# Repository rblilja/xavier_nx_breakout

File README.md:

# xavier_nx_breakout
Header breakout for NVIDIA Jetson Xavier NX Development Kit.

This breakout board overcomes the limitation of the 2uA maximum output current (per pin) of the TXB0108 8-Bit Bidirectional Voltage-Level Translators used for the GPIOs of the J12 header.

The breakout provides the following:

* UART1_TX and UART1_RTS buffered with non-inverting Schmitt triggers.
* PWM capable GPIO07, GPIO12 and GPIO13 buffered with non-inverting Schmitt triggers.
* Pixhawk compatible interface (JST-GH 6-pin 1.25 mm pitch) provided for UART1.
* Stemma QT / Qwiic (JST-SH 4-pin 1.0 mm pitch) compatible interface provided for I2C0.
* Pixhawk compatible interface (JST-GH 4-pin 1.25 mm pitch) provided for I2C1.

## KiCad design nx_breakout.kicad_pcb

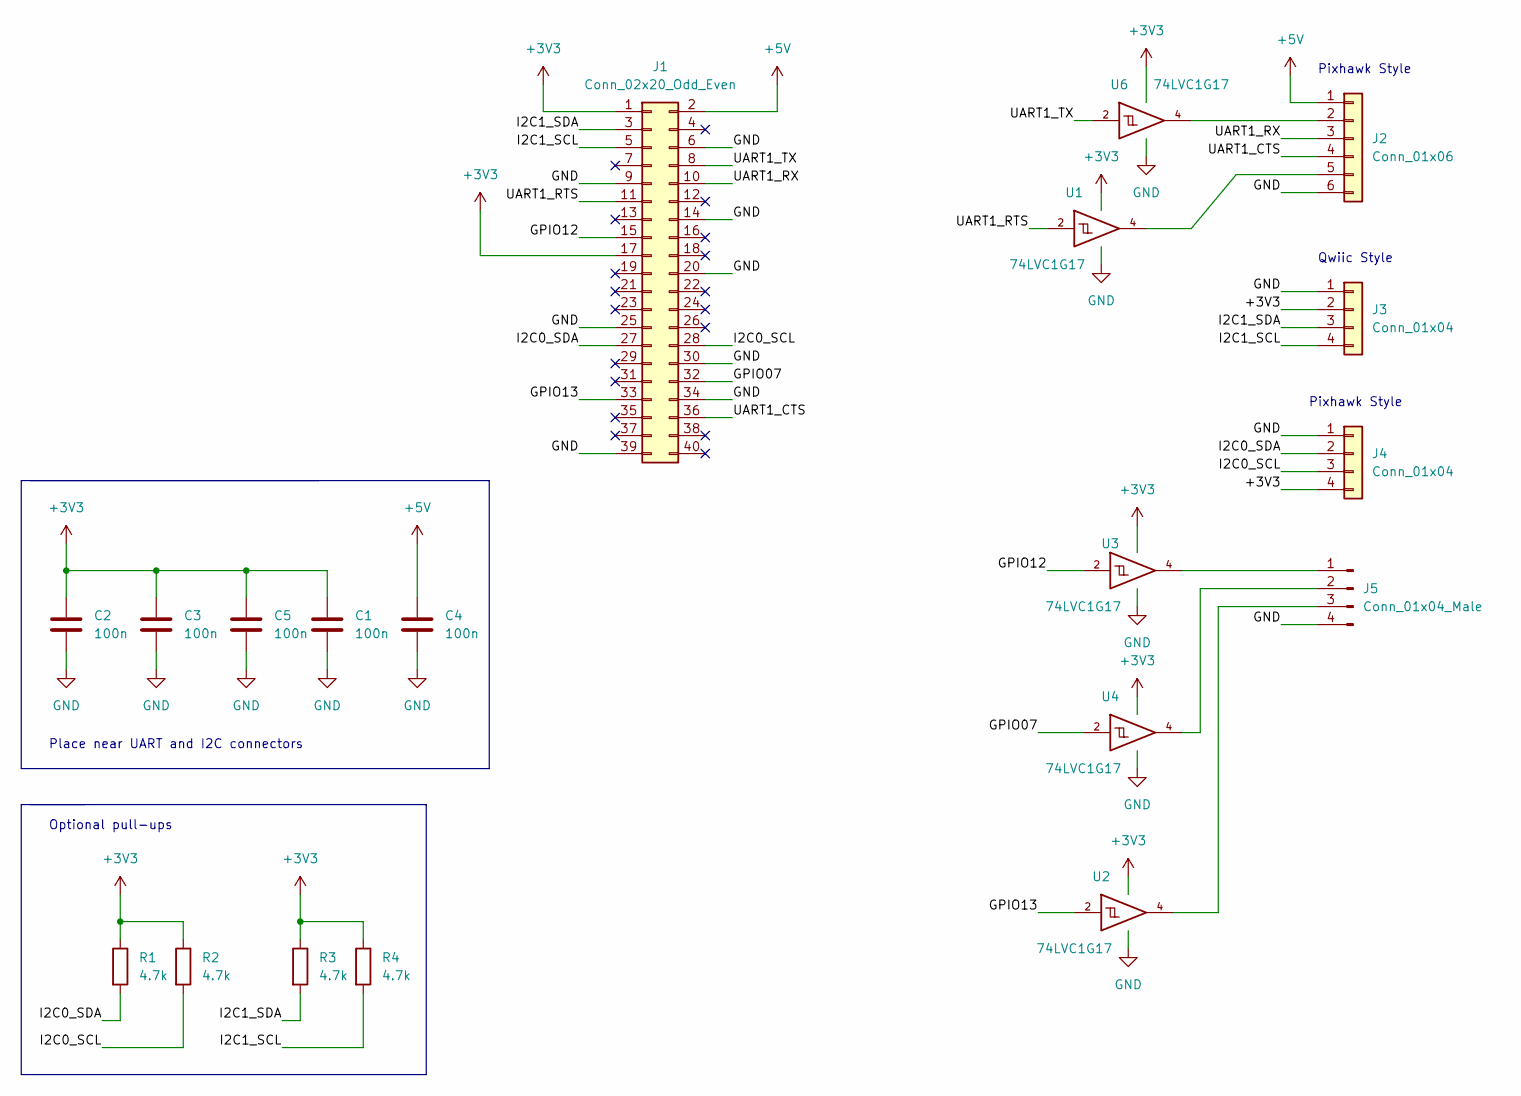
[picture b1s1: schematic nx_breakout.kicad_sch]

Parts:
C1, C2, C3, C4, C5: 100n; C_0603_1608Metric_Pad1.08x0.95mm_HandSolder
J1: Conn_02x20_Odd_Even; PinSocket_2x20_P2.54mm_Horizontal
J2: Conn_01x06; JST_GH_BM06B-GHS-TBT_1x06-1MP_P1.25mm_Vertical
J3: Conn_01x04; JST_SH_BM04B-SRSS-TB_1x04-1MP_P1.00mm_Vertical
J4: Conn_01x04; JST_GH_BM04B-GHS-TBT_1x04-1MP_P1.25mm_Vertical
J5: Conn_01x04_Male; PinHeader_1x04_P2.54mm_Vertical
R1, R2, R3, R4: 4.7k; R_0603_1608Metric_Pad0.98x0.95mm_HandSolder
U1, U2, U3, U4, U6: 74LVC1G17; SOT-23-5_HandSoldering

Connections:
+3V3: C1.1, C2.1, C3.1, C5.1, J1.1, J1.17, J3.2, J4.4, R1.1, R2.1, R3.1, R4.1, U1.5 (VCC), U2.5 (VCC), U3.5 (VCC), U4.5 (VCC), U6.5 (VCC)
+5V: C4.1, J1.2, J2.1
/GPIO07: J1.32, U4.2
/GPIO12: J1.15, U3.2
/GPIO13: J1.33, U2.2
/I2C0_SCL: J1.28, J4.3, R2.2
/I2C0_SDA: J1.27, J4.2, R1.2
/I2C1_SCL: J1.5, J3.4, R4.2
/I2C1_SDA: J1.3, J3.3, R3.2
/UART1_CTS: J1.36, J2.4
/UART1_RTS: J1.11, U1.2
/UART1_RX: J1.10, J2.3
/UART1_TX: J1.8, U6.2
GND: C1.2, C2.2, C3.2, C4.2, C5.2, J1.6, J1.9, J1.14, J1.20, J1.25, J1.30, J1.34, J1.39, J2.6, J3.1, J4.1, J5.4, U1.3 (GND), U2.3 (GND), U3.3 (GND), U4.3 (GND), U6.3 (GND)
unnamed: J2.5, U1.4
unnamed: J5.1, U3.4
unnamed: J5.2, U4.4
unnamed: J5.3, U2.4
unnamed: J2.2, U6.4

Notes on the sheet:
Place near UART and I2C connectors
Pixhawk Style
Qwiic Style
Optional pull-ups

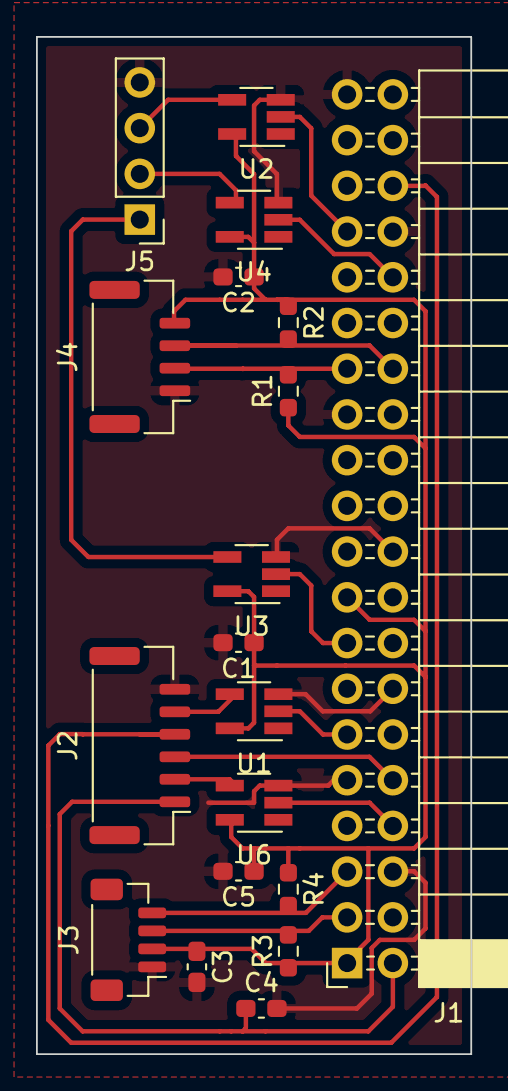
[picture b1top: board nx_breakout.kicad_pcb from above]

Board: 2 copper layers, 24.1 x 56.5 mm, 19 parts (0 on the bottom side), 19 nets.

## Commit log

2022-05-08 Add files via upload
    Corrected to non-inverting Schmitt triggers.
